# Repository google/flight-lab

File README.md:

# Flight Lab

Flight Lab is a project to build high fidelity flight simulation experience.

Disclaimer: This is not an officially supported Google product.

# Flight Lab Repository

This repository contains complete spec, design, model, source code of software
and firmware to build a flight simulation system.

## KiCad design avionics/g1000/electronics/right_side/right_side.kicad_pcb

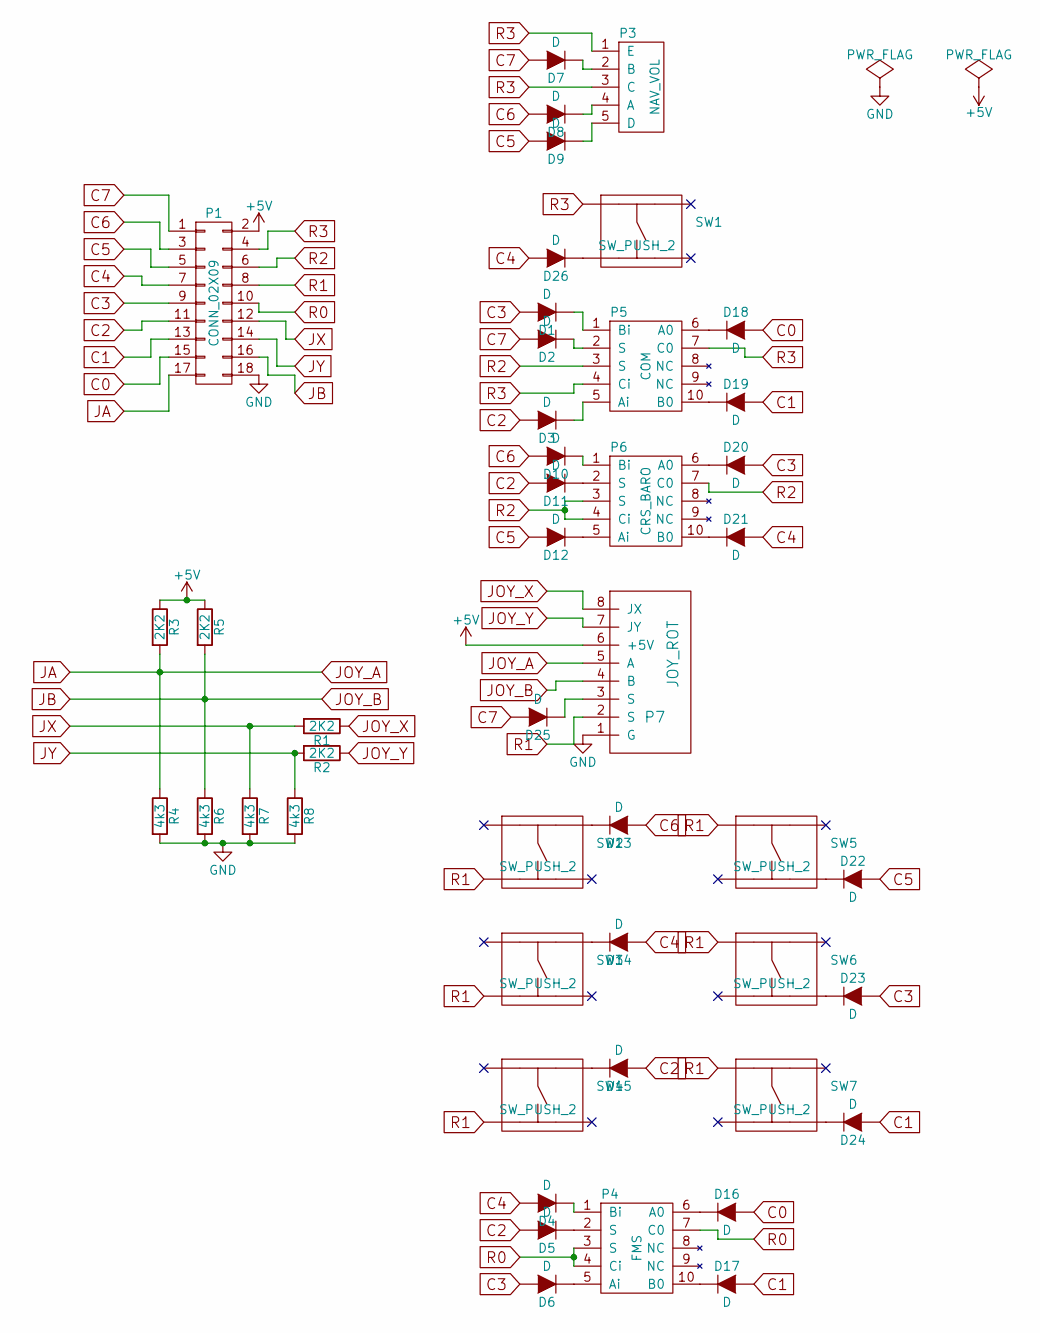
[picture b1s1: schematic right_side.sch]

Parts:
D1, D2, D3, D4, D5, D6, D7, D8, D9, D10, D11, D12, D13, D14, D15, D16, D17, D18, D19, D20, D21, D22, D23, D24, D25, D26: D; Diode_SMD
P1: CONN_02X09; CNC-3020-18
P3: NAV_VOL; ENC_conn
P4: FMS; ELMA_conn
P5: COM; ELMA_conn
P6: CRS_BARO; ELMA_conn
P7: JOY_ROT
R1, R2, R3, R5: 2K2; R_0805
R4, R6, R7, R8: 4k3; R_0805
SW1, SW2, SW3, SW4, SW5, SW6, SW7: SW_PUSH_2; SW_PUSH

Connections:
+5V: P1.2, P7.6 (+5V), R3.1, R5.1
C0: D16.2 (A), D18.2 (A), P1.15
C1: D17.2 (A), D19.2 (A), D24.2 (A), P1.13
C2: D3.2 (A), D5.2 (A), D11.2 (A), D15.2 (A), P1.11
C3: D1.2 (A), D6.2 (A), D20.2 (A), D23.2 (A), P1.9
C4: D4.2 (A), D14.2 (A), D21.2 (A), D26.2 (A), P1.7
C5: D9.2 (A), D12.2 (A), D22.2 (A), P1.5
C6: D8.2 (A), D10.2 (A), D13.2 (A), P1.3
C7: D2.2 (A), D7.2 (A), D25.2 (A), P1.1
GND: P1.18, P7.1 (G), R4.2, R6.2, R7.2, R8.2
JA: P1.17, P7.5 (A), R3.2, R4.1
JB: P1.16, P7.4 (B), R5.2, R6.1
JOY_X: P7.8 (JX), R1.1
JOY_Y: P7.7 (JY), R2.1
JX: P1.12, R1.2, R7.1
JY: P1.14, R2.2, R8.1
unnamed: D1.1 (K), P5.1 (Bi)
unnamed: D2.1 (K), P5.2 (S)
unnamed: D3.1 (K), P5.5 (Ai)
unnamed: D4.1 (K), P4.1 (Bi)
unnamed: D5.1 (K), P4.2 (S)
unnamed: D6.1 (K), P4.5 (Ai)
unnamed: D7.1 (K), P3.2 (B)
unnamed: D8.1 (K), P3.4 (A)
unnamed: D9.1 (K), P3.5 (D)
unnamed: D10.1 (K), P6.1 (Bi)
unnamed: D11.1 (K), P6.2 (S)
unnamed: D12.1 (K), P6.5 (Ai)
unnamed: D13.1 (K), SW2.2
unnamed: D14.1 (K), SW3.2
unnamed: D15.1 (K), SW4.2
unnamed: D16.1 (K), P4.6 (A0)
unnamed: D17.1 (K), P4.10 (B0)
unnamed: D18.1 (K), P5.6 (A0)
unnamed: D19.1 (K), P5.10 (B0)
unnamed: D20.1 (K), P6.6 (A0)
unnamed: D21.1 (K), P6.10 (B0)
unnamed: D22.1 (K), SW5.4
unnamed: D23.1 (K), SW6.4
unnamed: D24.1 (K), SW7.4
unnamed: D25.1 (K), P7.3 (S)
unnamed: D26.1 (K), SW1.3
R0: P1.10, P4.3 (S), P4.4 (Ci), P4.7 (C0)
R1: P1.8, P7.2 (S), SW2.3, SW3.3, SW4.3, SW5.1, SW6.1, SW7.1
R2: P1.6, P5.3 (S), P6.3 (S), P6.4 (Ci), P6.7 (C0)
R3: P1.4, P3.1 (E), P3.3 (C), P5.4 (Ci), P5.7 (C0), SW1.1

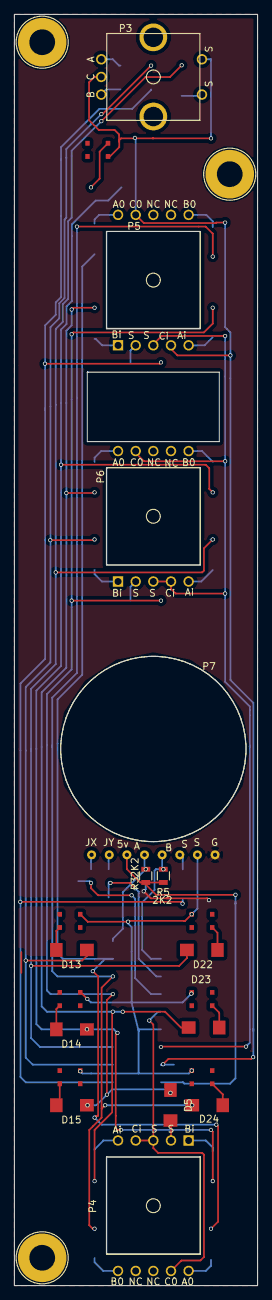
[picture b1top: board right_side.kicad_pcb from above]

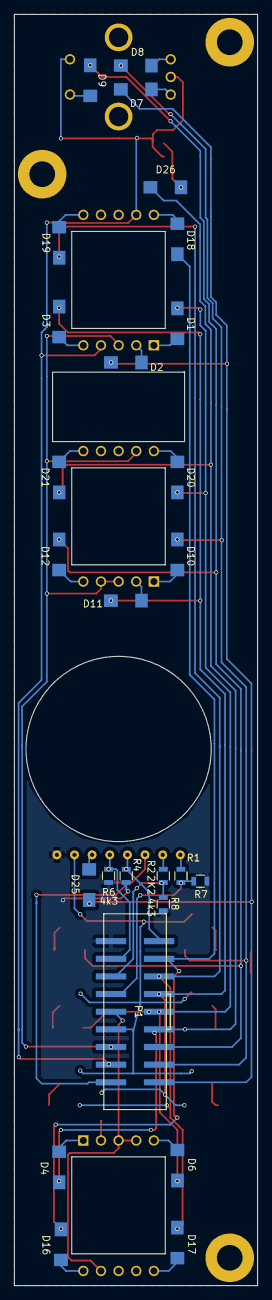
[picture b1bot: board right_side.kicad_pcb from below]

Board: 2 copper layers, 35.0 x 183.0 mm, 50 parts (26 on the bottom side), 46 nets.

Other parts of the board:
Ref**: Val**; SCREW
Ref**#2, Ref**#3: Val**; SCREW

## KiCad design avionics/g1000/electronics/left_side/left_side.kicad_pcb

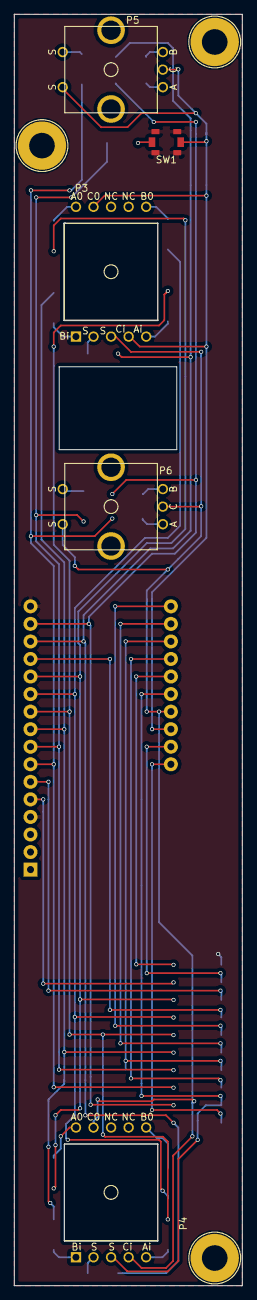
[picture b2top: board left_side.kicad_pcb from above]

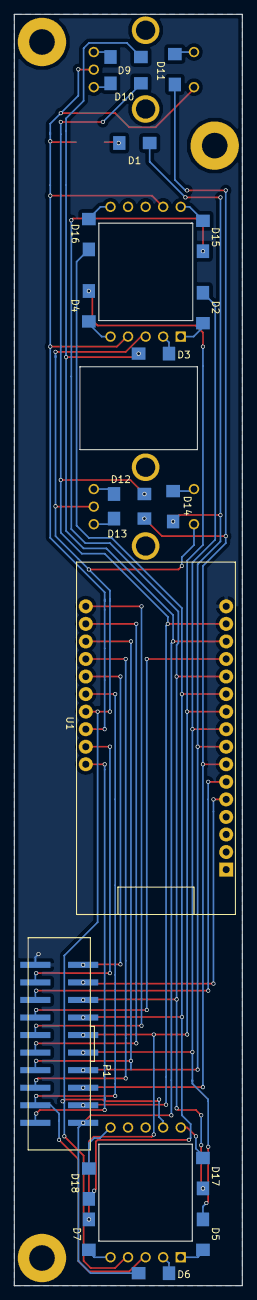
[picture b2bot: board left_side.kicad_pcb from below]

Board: 2 copper layers, 33.0 x 184.0 mm, 27 parts (19 on the bottom side), 39 nets.

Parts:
D1: D; Diode_SMD
D2, D3, D4, D5, D6, D7, D9, D10, D11, D12, D13, D14, D15, D16, D17, D18: Diode_SMD
P1: CONN_02X10; CNC-3020-20
P3: DUAL_NAV; ELMA_conn
P4: ALT; ELMA_conn
P5: NAV_VOL; ENC_conn
P6: HEADING; ENC_conn
Ref**: Val**; SCREW
Ref**#2, Ref**#3: Val**; SCREW
SW1: NAV_TOGGLE; SW_PUSH_GND
U1: Feather_M0

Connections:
+5V: P1.2, U1.26
C0: D15.2, D17.2, P1.15, U1.12
C1: D16.2, D18.2, P1.13, U1.11
C2: D4.2, D7.2, P1.11, U1.10
C3: D2.2, D5.2, P1.9, U1.9
C4: D1.2, D14.2, P1.7, U1.8
C5: D11.2, D13.2, P1.5, U1.7
C6: D10.2, D12.2, P1.3, U1.15
C7: D3.2, D6.2, D9.2, P1.1, U1.14
GND: P1.20, SW1.3, SW1.4, SW1.5, SW1.6, U1.4, U1.16
JA: P1.19, U1.21
JB: P1.18, U1.17
JX: P1.17, U1.5
JY: P1.16, U1.6
unnamed: D1.1, SW1.1
unnamed: D2.1, P3.1
unnamed: D3.1, P3.2
unnamed: D4.1, P3.5
unnamed: D5.1, P4.1
unnamed: D6.1, P4.2
unnamed: D7.1, P4.5
unnamed: D9.1, P5.2
unnamed: D10.1, P5.4
unnamed: D11.1, P5.5
unnamed: D12.1, P6.2
unnamed: D13.1, P6.4
unnamed: D14.1, P6.5
unnamed: D15.1, P3.6
unnamed: D16.1, P3.10
unnamed: D17.1, P4.6
unnamed: D18.1, P4.10
R0: P1.14, U1.13
R1: P1.12, U1.25
R2: P1.10, U1.24
R3: P1.8, U1.23
R4: P1.6, U1.22
R5: P1.4, P4.3, U1.20
R6: P3.3, P4.4, P4.7, P6.1, P6.3, U1.19
R7: P3.4, P3.7, P5.1, P5.3, SW1.2, U1.18

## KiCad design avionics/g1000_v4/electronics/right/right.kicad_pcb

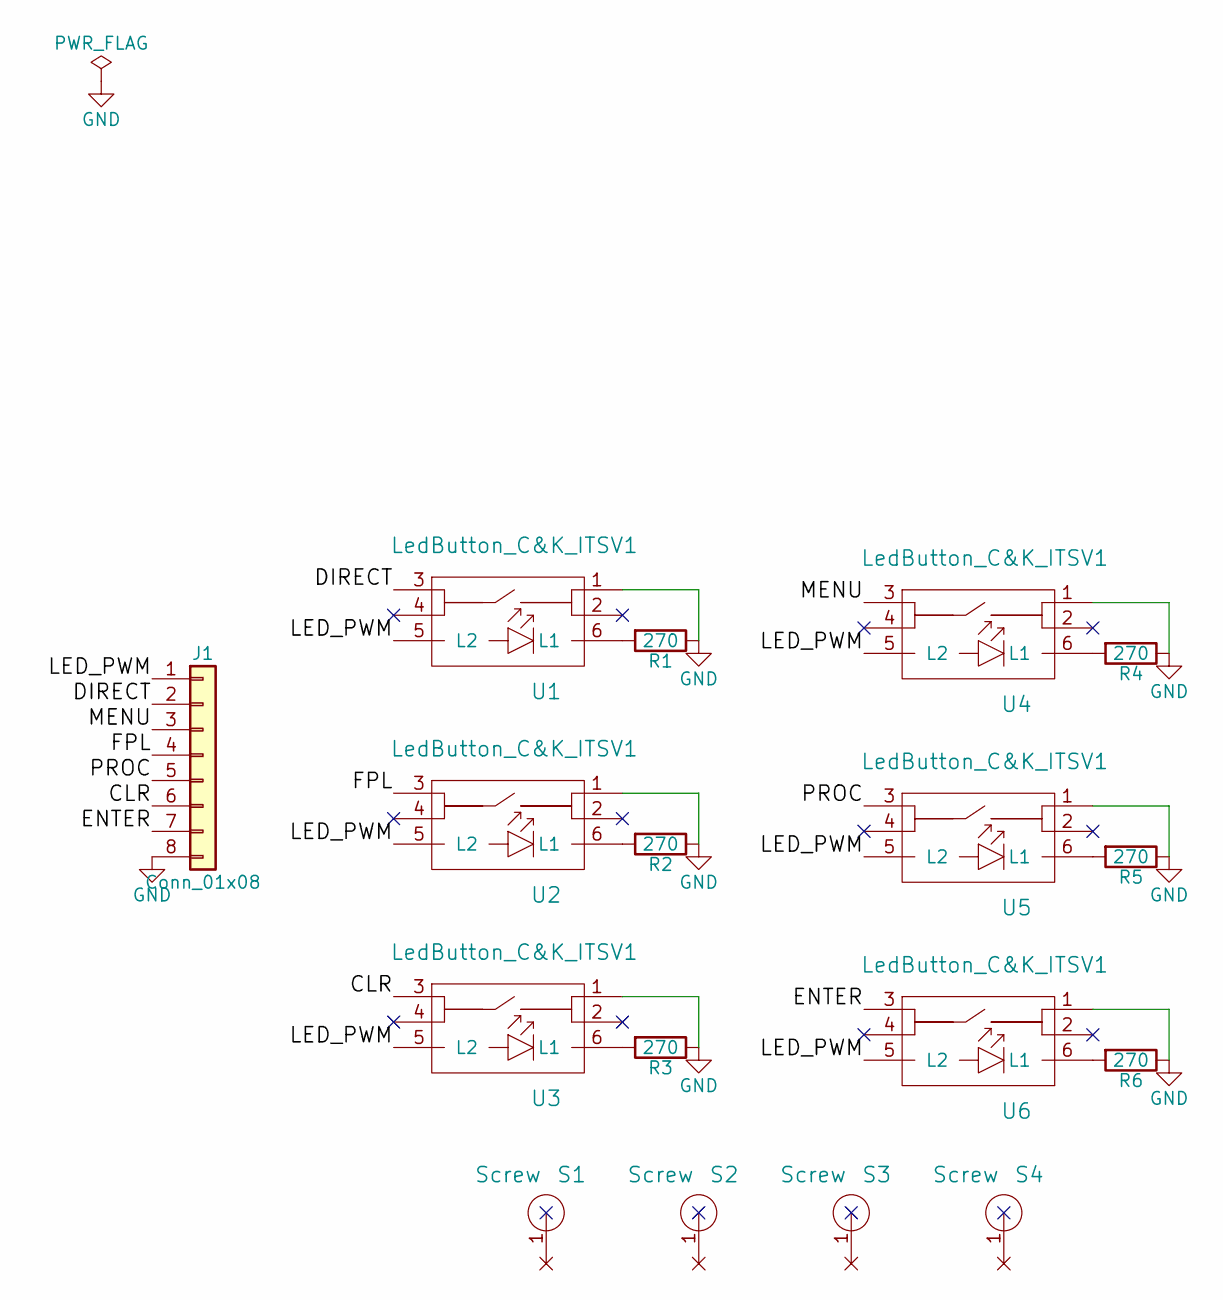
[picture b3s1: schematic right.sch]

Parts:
J1: Conn_01x08; Pin_Header_Straight_1x08_Pitch2.54mm
R1, R2, R3, R4, R5, R6: 270; R_0805_HandSoldering
S1, S2, S3, S4: Screw; SCREW_M3
U1, U2, U3, U4, U5, U6: LedButton_C&K_ITSV1

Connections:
/CLR: J1.6, U3.3
/DIRECT: J1.2, U1.3
/ENTER: J1.7, U6.3
/FPL: J1.4, U2.3
/LED_PWM: J1.1, U1.5 (L2), U2.5 (L2), U3.5 (L2), U4.5 (L2), U5.5 (L2), U6.5 (L2)
/MENU: J1.3, U4.3
/PROC: J1.5, U5.3
GND: J1.8, R1.1, R2.1, R3.1, R4.1, R5.1, R6.1, U1.1, U2.1, U3.1, U4.1, U5.1, U6.1
unnamed: R1.2, U1.6 (L1)
unnamed: R2.2, U2.6 (L1)
unnamed: R3.2, U3.6 (L1)
unnamed: R4.2, U4.6 (L1)
unnamed: R5.2, U5.6 (L1)
unnamed: R6.2, U6.6 (L1)

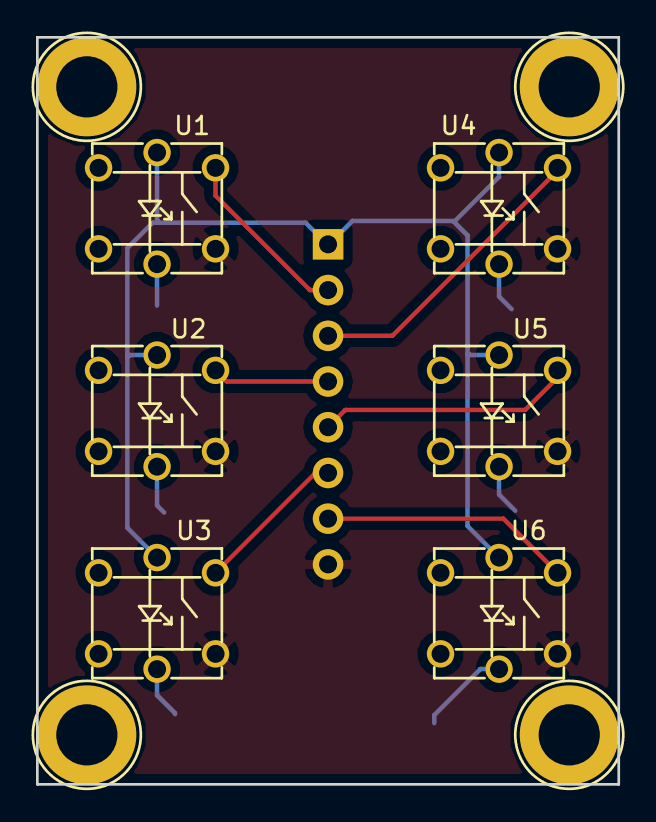
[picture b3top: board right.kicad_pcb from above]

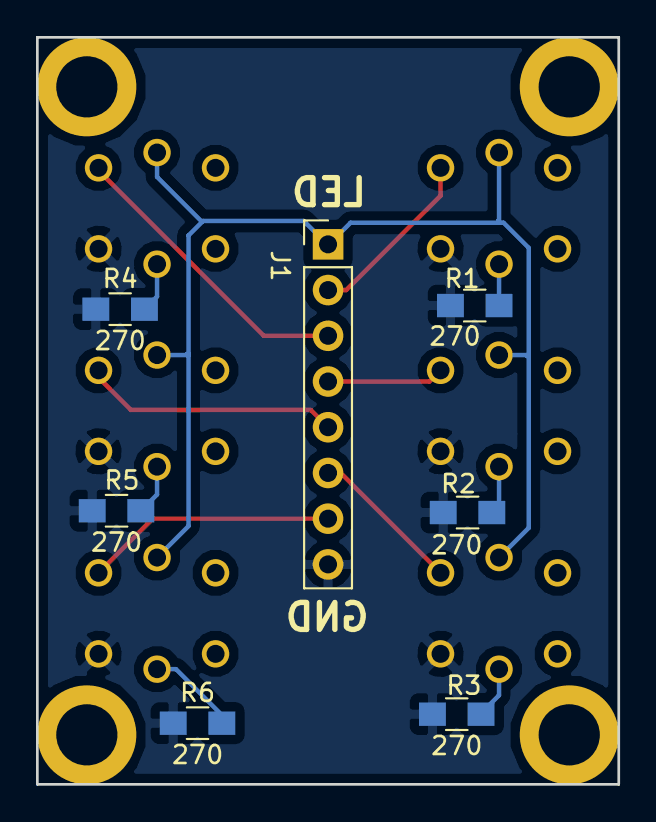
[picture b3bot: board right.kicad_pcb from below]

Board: 2 copper layers, 32.3 x 41.5 mm, 17 parts (7 on the bottom side), 14 nets.

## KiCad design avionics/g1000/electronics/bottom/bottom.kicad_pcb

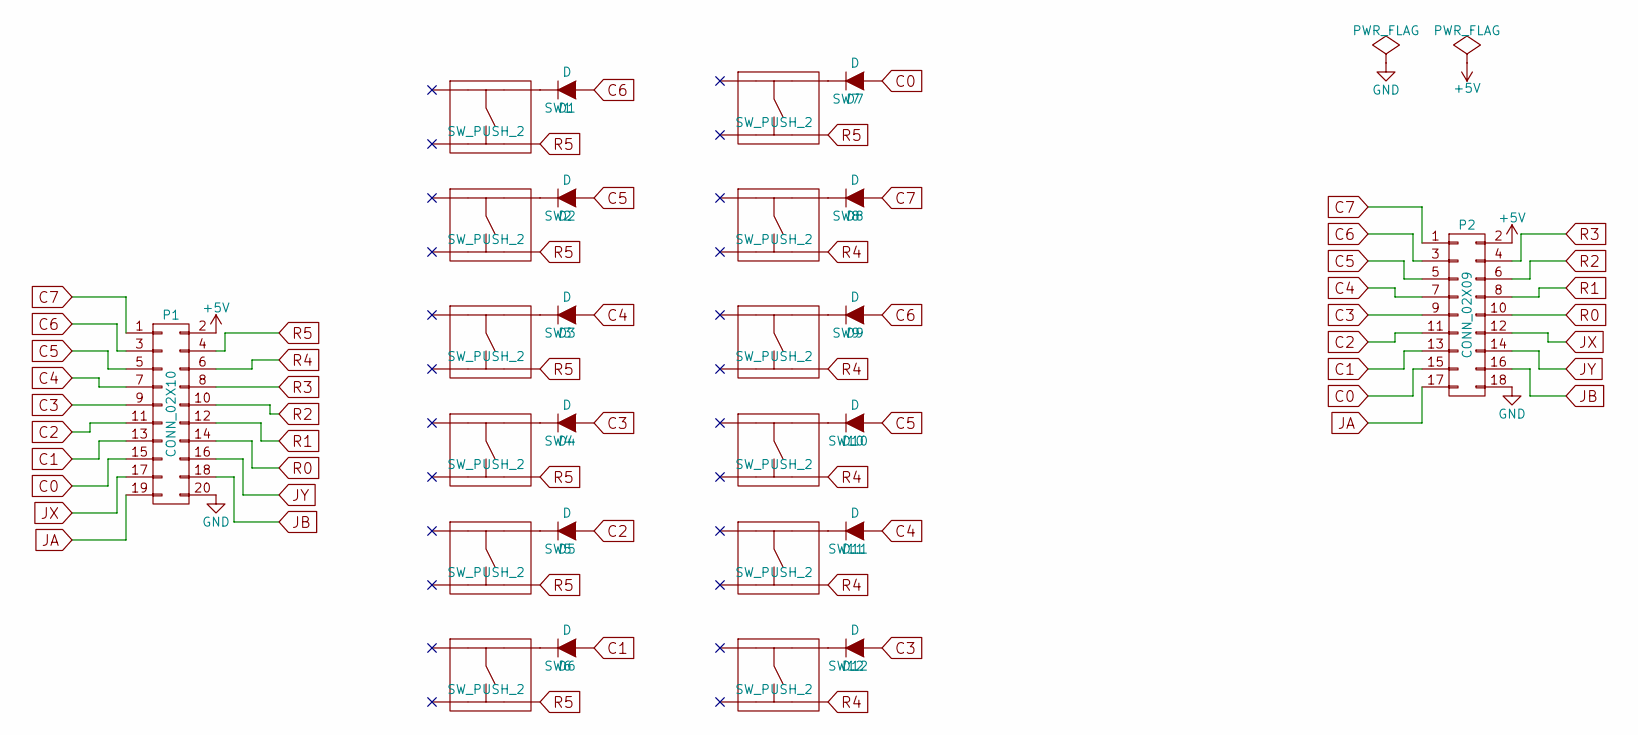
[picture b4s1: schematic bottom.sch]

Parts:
D1, D2, D3, D4, D5, D6, D7, D8, D9, D10, D11, D12: D; Diode_SMD
P1: CONN_02X10; CNC-3020-20
P2: CONN_02X09; CNC-3020-18
SW1, SW2, SW3, SW4, SW5, SW6, SW7, SW8, SW9, SW10, SW11, SW12: SW_PUSH_2; SW_PUSH

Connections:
+5V: P1.2, P2.2
C0: D7.2 (A), P1.15, P2.15
C1: D6.2 (A), P1.13, P2.13
C2: D5.2 (A), P1.11, P2.11
C3: D4.2 (A), D12.2 (A), P1.9, P2.9
C4: D3.2 (A), D11.2 (A), P1.7, P2.7
C5: D2.2 (A), D10.2 (A), P1.5, P2.5
C6: D1.2 (A), D9.2 (A), P1.3, P2.3
C7: D8.2 (A), P1.1, P2.1
GND: P1.20, P2.18
JA: P1.19, P2.17
JB: P1.18, P2.16
JX: P1.17, P2.12
JY: P1.16, P2.14
unnamed: D1.1 (K), SW1.2
unnamed: D2.1 (K), SW2.2
unnamed: D3.1 (K), SW3.2
unnamed: D4.1 (K), SW4.2
unnamed: D5.1 (K), SW5.2
unnamed: D6.1 (K), SW6.2
unnamed: D7.1 (K), SW7.2
unnamed: D8.1 (K), SW8.2
unnamed: D9.1 (K), SW9.2
unnamed: D10.1 (K), SW10.2
unnamed: D11.1 (K), SW11.2
unnamed: D12.1 (K), SW12.2
R0: P1.14, P2.10
R1: P1.12, P2.8
R2: P1.10, P2.6
R3: P1.8, P2.4
R4: P1.6, SW8.4, SW9.4, SW10.4, SW11.4, SW12.4
R5: P1.4, SW1.4, SW2.4, SW3.4, SW4.4, SW5.4, SW6.4, SW7.4

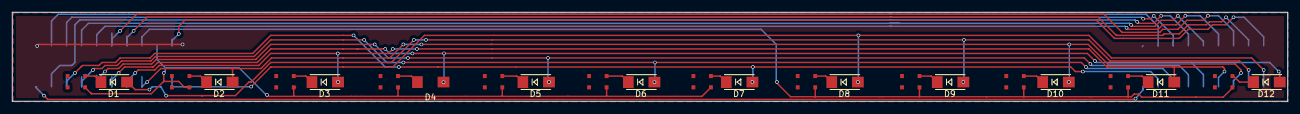
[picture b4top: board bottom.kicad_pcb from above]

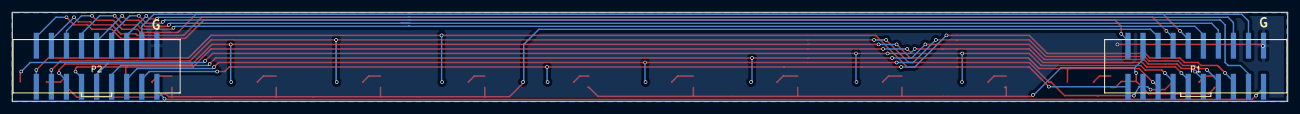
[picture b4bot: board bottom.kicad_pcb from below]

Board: 2 copper layers, 215.0 x 15.0 mm, 26 parts (2 on the bottom side), 32 nets.

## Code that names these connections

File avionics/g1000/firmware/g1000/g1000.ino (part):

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const PROGMEM char RANGE_PAN_LEFT[] = "PFD_RANGE_PAN_LEFT";
const PROGMEM char RANGE_PAN_RIGHT[] = "PFD_RANGE_PAN_RIGHT";
const PROGMEM char DIRECT_TO[] = "PFD_DIRECT_TO";
const PROGMEM char MENU[] = "PFD_MENU";
const PROGMEM char FPL[] = "PFD_FPL";
const PROGMEM char PROC[] = "PFD_PROC";
const PROGMEM char CLR[] = "PFD_CLR";
const PROGMEM char ENT[] = "PFD_ENT";
const PROGMEM char LARGE_FMS_INCR[] = "PFD_LARGE_FMS_INCR";
const PROGMEM char LARGE_FMS_DECR[] = "PFD_LARGE_FMS_DECR";
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const PROGMEM char RANGE_PAN_LEFT[] = "MFD_RANGE_PAN_LEFT";
const PROGMEM char RANGE_PAN_RIGHT[] = "MFD_RANGE_PAN_RIGHT";
const PROGMEM char DIRECT_TO[] = "MFD_DIRECT_TO";
const PROGMEM char MENU[] = "MFD_MENU";
const PROGMEM char FPL[] = "MFD_FPL";
const PROGMEM char PROC[] = "MFD_PROC";
const PROGMEM char CLR[] = "MFD_CLR";
const PROGMEM char ENT[] = "MFD_ENT";
const PROGMEM char LARGE_FMS_INCR[] = "MFD_LARGE_FMS_INCR";
const PROGMEM char LARGE_FMS_DECR[] = "MFD_LARGE_FMS_DECR";
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
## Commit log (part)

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2018-09-13 Initialize repo with licensing info and readme.
2018-09-14 Make controller to work on linux.
2018-09-17 Fix: update App and WindowsApp status correctly
2018-09-17 Regenerate protos
2018-09-21 Set theme jekyll-theme-minimal
2018-09-27 Remove debug print
2018-09-27 Revert "Set theme jekyll-theme-minimal"
    This reverts commit e381bfb86cdcf90bb6c9be07222cb2059a43bfb7.
2018-09-30 Hide the scroll bar.
2018-10-06 update email documentation
2018-10-06 update send bug button state.
2018-10-12 Tweak auto start mechanism
2018-10-12 Update badger component based on review feedback
2018-10-12 Fix indentation of deauth to ensure it always runs
2018-10-12 add badge reader support
2018-10-12 move badge reader url to backend url
2018-11-07 add GetConfig() gRPC interface
2018-11-08 Use streaming in the status table. Add project.config.js back to gitignore.
2018-11-08 refresh gitignore
2018-12-06 PCBs for new G1000 partially complete.
2018-12-07 Adding support for magnetic encoder. Compiles but doesn't work yet.
2019-01-22 Fix Makefile and service templates
2019-01-22 Fix incorrect text encoding
2019-01-22 Bug fixes and minor improvement to app component
2019-03-04 Rearrange switch panel firmware code.
2020-09-04 Bump showdown from 1.8.6 to 1.9.1 in /ui
    Bumps [showdown](https://github.com/showdownjs/showdown) from 1.8.6 to 1.9.1.
    - [Release notes](https://github.com/showdownjs/showdown/releases)
    - [Changelog](https://github.com/showdownjs/showdown/blob/1.9.1/CHANGELOG.md)
    - [Commits](https://github.com/showdownjs/showdown/compare/1.8.6...1.9.1)
2021-03-03 Bump pug from 2.0.3 to 3.0.1 in /ui
    Bumps [pug](https://github.com/pugjs/pug) from 2.0.3 to 3.0.1.
    - [Release notes](https://github.com/pugjs/pug/releases)
    - [Commits](https://github.com/pugjs/pug/compare/pug@2.0.3...pug@3.0.1)
2022-04-09 Bump moment from 2.22.2 to 2.29.2 in /ui
    Bumps [moment](https://github.com/moment/moment) from 2.22.2 to 2.29.2.
    - [Release notes](https://github.com/moment/moment/releases)
    - [Changelog](https://github.com/moment/moment/blob/develop/CHANGELOG.md)
    - [Commits](https://github.com/moment/moment/compare/2.22.2...2.29.2)
    ---
    updated-dependencies:
2022-10-05 Bump css-what from 2.1.0 to 6.1.0 in /ui
    Bumps [css-what](https://github.com/fb55/css-what) from 2.1.0 to 6.1.0.
    - [Release notes](https://github.com/fb55/css-what/releases)
    - [Commits](https://github.com/fb55/css-what/compare/v2.1.0...v6.1.0)
    ---
    updated-dependencies:
    - dependency-name: css-what
2022-12-02 Bump decode-uri-component from 0.2.0 to 0.2.2 in /ui/functions
    Bumps [decode-uri-component](https://github.com/SamVerschueren/decode-uri-component) from 0.2.0 to 0.2.2.
    - [Release notes](https://github.com/SamVerschueren/decode-uri-component/releases)
    - [Commits](https://github.com/SamVerschueren/decode-uri-component/compare/v0.2.0...v0.2.2)
    ---
    updated-dependencies:
    - dependency-name: decode-uri-component
2022-12-07 Bump qs and express in /ui
    Bumps [qs](https://github.com/ljharb/qs), [qs](https://github.com/ljharb/qs) and [express](https://github.com/expressjs/express). These dependencies needed to be updated together.
    Updates `qs` from 6.5.1 to 6.11.0
    - [Release notes](https://github.com/ljharb/qs/releases)
    - [Changelog](https://github.com/ljharb/qs/blob/main/CHANGELOG.md)
    - [Commits](https://github.com/ljharb/qs/compare/v6.5.1...v6.11.0)
    Updates `qs` from 6.5.2 to 6.11.0
2022-12-08 Bump express from 4.16.3 to 4.18.2 in /ui
    Bumps [express](https://github.com/expressjs/express) from 4.16.3 to 4.18.2.
    - [Release notes](https://github.com/expressjs/express/releases)
    - [Changelog](https://github.com/expressjs/express/blob/master/History.md)
    - [Commits](https://github.com/expressjs/express/compare/4.16.3...4.18.2)
    ---
    updated-dependencies:
2023-03-02 Bump minimist and mkdirp in /ui/functions
    Bumps [minimist](https://github.com/minimistjs/minimist) and [mkdirp](https://github.com/isaacs/node-mkdirp). These dependencies needed to be updated together.
    Updates `minimist` from 1.2.0 to 1.2.8
    - [Release notes](https://github.com/minimistjs/minimist/releases)
    - [Changelog](https://github.com/minimistjs/minimist/blob/main/CHANGELOG.md)
    - [Commits](https://github.com/minimistjs/minimist/compare/v1.2.0...v1.2.8)
    Updates `mkdirp` from 0.5.1 to 0.5.6
2023-03-23 This is a bug bounty test. Please ignore.. (fcrzbd)
2023-04-29 Bump postcss from 5.2.18 to 7.0.36 in /ui
    Bumps [postcss](https://github.com/postcss/postcss) from 5.2.18 to 7.0.36.
    - [Release notes](https://github.com/postcss/postcss/releases)
    - [Changelog](https://github.com/postcss/postcss/blob/main/CHANGELOG.md)
    - [Commits](https://github.com/postcss/postcss/commits/7.0.36)
    ---
    updated-dependencies:
2023-04-29 Bump hawk from 6.0.2 to in /ui
    Bumps [hawk](https://github.com/mozilla/hawk) from 6.0.2 to .
    - [Release notes](https://github.com/mozilla/hawk/releases)
    - [Commits](https://github.com/mozilla/hawk/commits)
    ---
    updated-dependencies:
    - dependency-name: hawk
2023-10-03 Bump postcss from 5.2.18 to 8.4.31 in /ui
    Bumps [postcss](https://github.com/postcss/postcss) from 5.2.18 to 8.4.31.
    - [Release notes](https://github.com/postcss/postcss/releases)
    - [Changelog](https://github.com/postcss/postcss/blob/main/CHANGELOG.md)
    - [Commits](https://github.com/postcss/postcss/commits/8.4.31)
    ---
    updated-dependencies:
2023-10-25 Bump lodash from 4.17.10 to 4.17.21 in /ui/functions
    Bumps [lodash](https://github.com/lodash/lodash) from 4.17.10 to 4.17.21.
    - [Release notes](https://github.com/lodash/lodash/releases)
    - [Commits](https://github.com/lodash/lodash/compare/4.17.10...4.17.21)
    ---
    updated-dependencies:
    - dependency-name: lodash
2023-10-26 Bump browserify-sign from 4.0.4 to 4.2.2 in /ui
    Bumps [browserify-sign](https://github.com/crypto-browserify/browserify-sign) from 4.0.4 to 4.2.2.
    - [Changelog](https://github.com/browserify/browserify-sign/blob/main/CHANGELOG.md)
    - [Commits](https://github.com/crypto-browserify/browserify-sign/compare/v4.0.4...v4.2.2)
    ---
    updated-dependencies:
    - dependency-name: browserify-sign
2023-11-10 Bump axios from 0.18.0 to 1.6.0 in /ui/functions
    Bumps [axios](https://github.com/axios/axios) from 0.18.0 to 1.6.0.
    - [Release notes](https://github.com/axios/axios/releases)
    - [Changelog](https://github.com/axios/axios/blob/v1.x/CHANGELOG.md)
    - [Commits](https://github.com/axios/axios/compare/v0.18.0...v1.6.0)
    ---
    updated-dependencies:
2023-12-04 Bump @google-cloud/firestore and firebase-admin in /ui/functions
    Bumps [@google-cloud/firestore](https://github.com/googleapis/nodejs-firestore) to 6.8.0 and updates ancestor dependency [firebase-admin](https://github.com/firebase/firebase-admin-node). These depen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
    Updates `@google-cloud/firestore` from 0.13.1 to 6.8.0
    - [Release notes](https://github.com/googleapis/nodejs-firestore/releases)
    - [Changelog](https://github.com/googleapis/nodejs-firestore/blob/main/CHANGELOG.md)
    - [Commits](https://github.com/googleapis/nodejs-firestore/compare/v0.13.1...v6.8.0)
    Updates `firebase-admin` from 5.10.0 to 11.11.1
2024-03-17 Bump follow-redirects from 1.5.0 to 1.15.6 in /ui/functions
    Bumps [follow-redirects](https://github.com/follow-redirects/follow-redirects) from 1.5.0 to 1.15.6.
    - [Release notes](https://github.com/follow-redirects/follow-redirects/releases)
    - [Commits](https://github.com/follow-redirects/follow-redirects/compare/v1.5.0...v1.15.6)
    ---
    updated-dependencies:
    - dependency-name: follow-redirects
2024-03-21 Bump webpack-dev-middleware and webpack-dev-server in /ui
    Removes [webpack-dev-middleware](https://github.com/webpack/webpack-dev-middleware). It's no longer used after updating ancestor dependency [webpack-dev-server](https://github.com/webpack/webpack-dev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
    Removes `webpack-dev-middleware`
    Updates `webpack-dev-server` from 2.11.2 to 5.0.4
    - [Release notes](https://github.com/webpack/webpack-dev-server/releases)
    - [Changelog](https://github.com/webpack/webpack-dev-server/blob/master/CHANGELOG.md)
    - [Commits](https://github.com/webpack/webpack-dev-server/compare/v2.11.2...v5.0.4)
2024-03-26 Bump express from 4.16.3 to 4.19.2 in /ui
    Bumps [express](https://github.com/expressjs/express) from 4.16.3 to 4.19.2.
    - [Release notes](https://github.com/expressjs/express/releases)
    - [Changelog](https://github.com/expressjs/express/blob/master/History.md)
    - [Commits](https://github.com/expressjs/express/compare/4.16.3...4.19.2)
    ---
    updated-dependencies:
2024-05-24 Bump url-parse from 1.4.0 to 1.5.10 in /ui
    Bumps [url-parse](https://github.com/unshiftio/url-parse) from 1.4.0 to 1.5.10.
    - [Commits](https://github.com/unshiftio/url-parse/compare/1.4.0...1.5.10)
    ---
    updated-dependencies:
    - dependency-name: url-parse
    dependency-type: indirect
2024-05-24 Bump set-value and union-value in /ui
    Bumps [set-value](https://github.com/jonschlinkert/set-value) and [union-value](https://github.com/jonschlinkert/union-value). These dependencies needed to be updated together.
    Updates `set-value` from 2.0.0 to 2.0.1
    - [Commits](https://github.com/jonschlinkert/set-value/compare/2.0.0...2.0.1)
    Updates `union-value` from 1.0.0 to 1.0.1
    - [Release notes](https://github.com/jonschlinkert/union-value/releases)
    - [Commits](https://github.com/jonschlinkert/union-value/compare/1.0.0...1.0.1)
2024-06-03 Bump the npm_and_yarn group across 2 directories with 41 updates
    Bumps the npm_and_yarn group with 26 updates in the /ui directory:
    | Package | From | To |
    | --- | --- | --- |
    | [axios](https://github.com/axios/axios) | `0.18.0` | `0.28.0` |
    | [moment](https://github.com/moment/moment) | `2.22.2` | `2.29.4` |
    | [postcss](https://github.com/postcss/postcss) | `5.2.18` | `8.4.31` |
2024-07-23 Bump extend from 3.0.1 to 3.0.2 in /ui
    Bumps [extend](https://github.com/justmoon/node-extend) from 3.0.1 to 3.0.2.
    - [Changelog](https://github.com/justmoon/node-extend/blob/main/CHANGELOG.md)
    - [Commits](https://github.com/justmoon/node-extend/compare/v3.0.1...v3.0.2)
    ---
    updated-dependencies:
    - dependency-name: extend
2024-07-23 Bump ini from 1.3.5 to 1.3.8 in /ui
    Bumps [ini](https://github.com/npm/ini) from 1.3.5 to 1.3.8.
    - [Release notes](https://github.com/npm/ini/releases)
    - [Changelog](https://github.com/npm/ini/blob/main/CHANGELOG.md)
    - [Commits](https://github.com/npm/ini/compare/v1.3.5...v1.3.8)
    ---
    updated-dependencies:
2024-07-23 Bump moment from 2.22.2 to 2.29.4 in /ui
    Bumps [moment](https://github.com/moment/moment) from 2.22.2 to 2.29.4.
    - [Changelog](https://github.com/moment/moment/blob/develop/CHANGELOG.md)
    - [Commits](https://github.com/moment/moment/compare/2.22.2...2.29.4)
    ---
    updated-dependencies:
    - dependency-name: moment

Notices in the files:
avionics/g1000/firmware/g1000/g1000.ino:
Copyright 2018 Flight Lab authors.
Licensed under the Apache License, Version 2.0 (the "License");
